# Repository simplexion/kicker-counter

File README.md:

# Kicker Counter
A simple way to digitize manual kicker counters.

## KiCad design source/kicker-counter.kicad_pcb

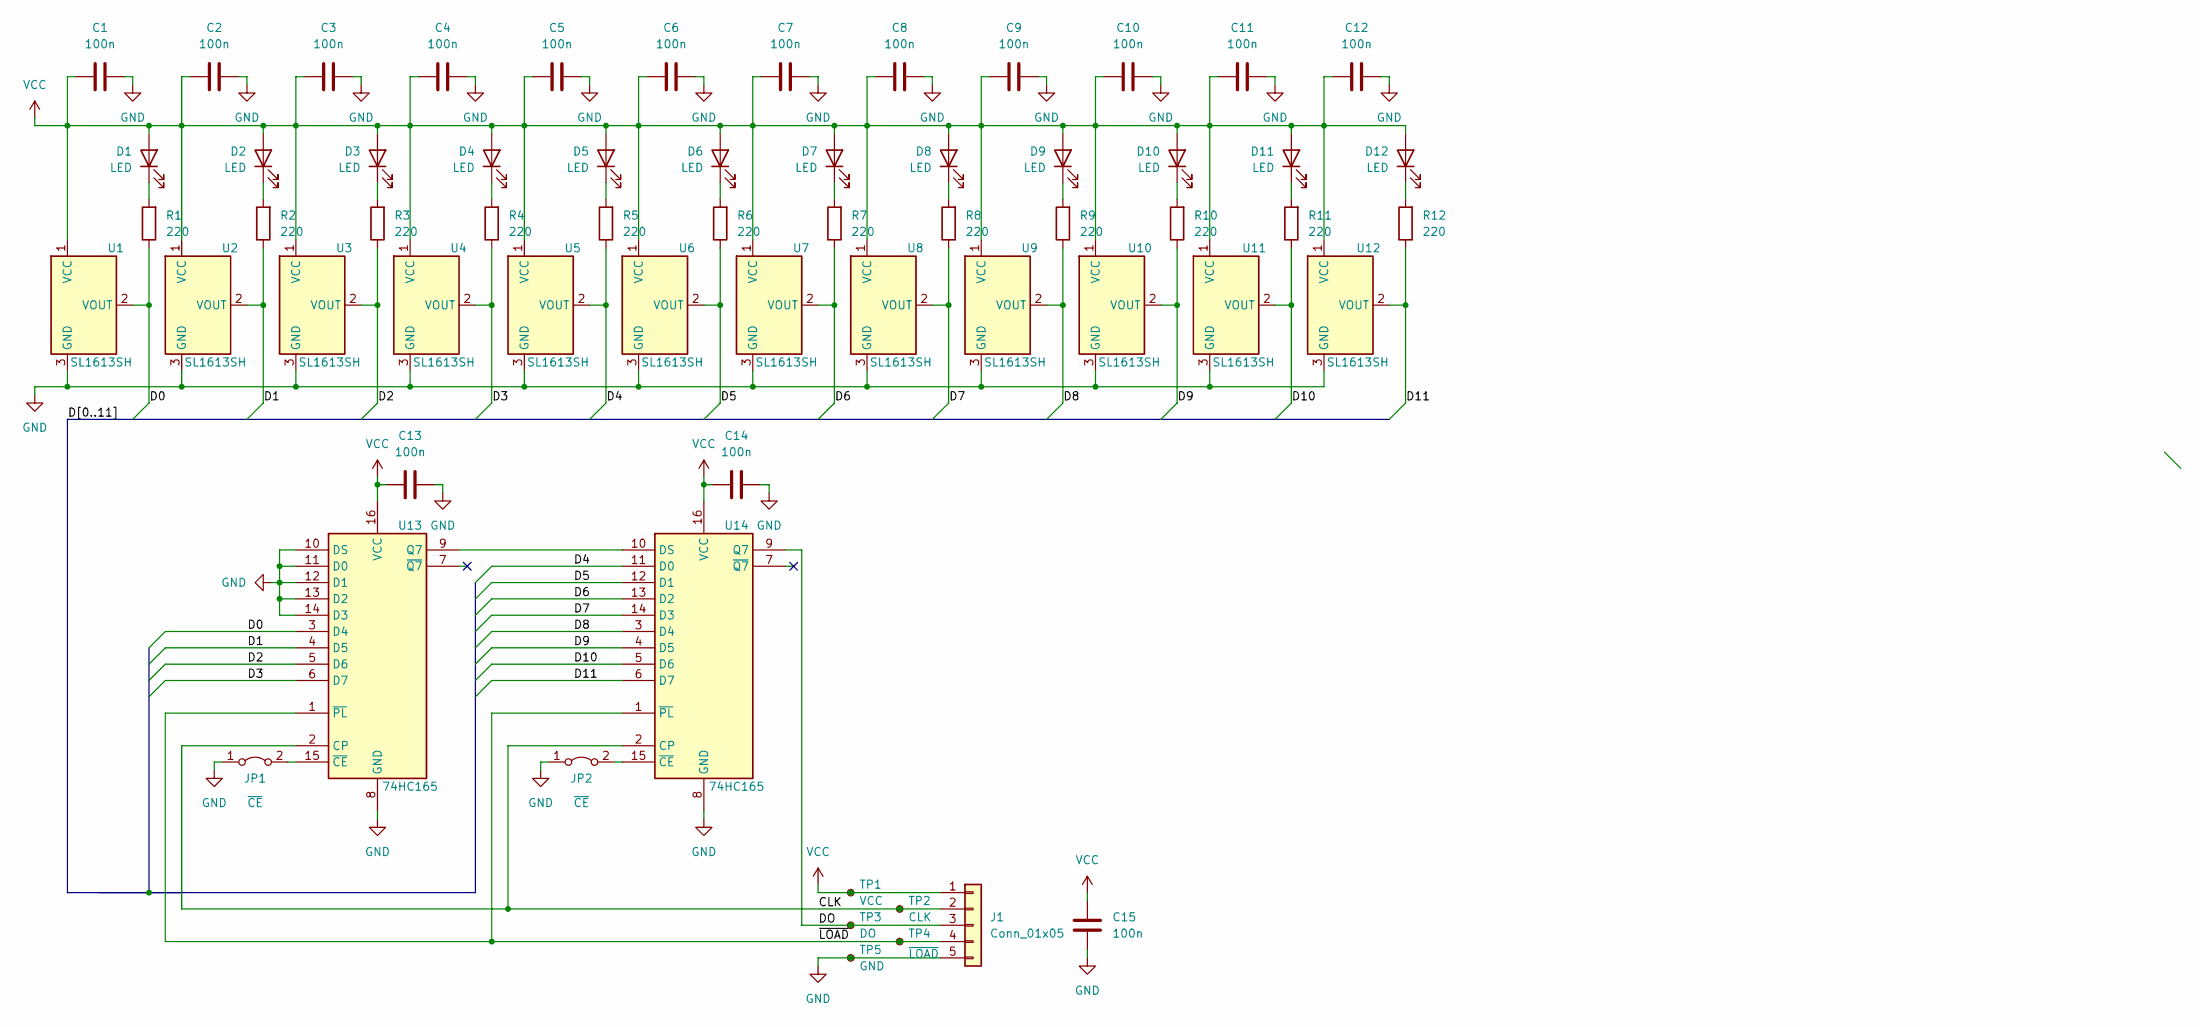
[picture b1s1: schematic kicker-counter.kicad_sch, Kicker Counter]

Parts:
C1, C2, C3, C4, C5, C6, C7, C8, C9, C10, C11, C12, C13, C14, C15: 100n; C_0603_1608Metric; LCSC C42998
D1, D2, D3, D4, D5, D6, D7, D8, D9, D10, D11, D12: LED; LED_0603_1608Metric; LCSC C2290
J1: Conn_01x05
JP1, JP2: ~{CE}; SolderJumper-2_P1.3mm_Bridged_RoundedPad1.0x1.5mm
R1, R2, R3, R4, R5, R6, R7, R8, R9, R10, R11, R12: 220; R_0603_1608Metric; LCSC C114683
TP1: VCC; TestPoint_THTPad_D1.5mm_Drill0.7mm
TP2: CLK; TestPoint_THTPad_D1.5mm_Drill0.7mm
TP3: DO; TestPoint_THTPad_D1.5mm_Drill0.7mm
TP4: ~{LOAD}; TestPoint_THTPad_D1.5mm_Drill0.7mm
TP5: GND; TestPoint_THTPad_D1.5mm_Drill0.7mm
U1, U2, U3, U4, U5, U6, U7, U8, U9, U10, U11, U12: SL1613SH; SOT-23; LCSC C498207
U13, U14: 74HC165; TSSOP-16_4.4x5mm_P0.65mm; LCSC C80696

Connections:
/CLK: J1.2, TP2.1, U13.2 (CP), U14.2 (CP)
/D0: R1.1, U1.2 (VOUT), U13.3 (D4)
/D1: R2.1, U2.2 (VOUT), U13.4 (D5)
/D2: R3.1, U3.2 (VOUT), U13.5 (D6)
/D3: R4.1, U4.2 (VOUT), U13.6 (D7)
/D4: R5.1, U5.2 (VOUT), U14.11 (D0)
/D5: R6.1, U6.2 (VOUT), U14.12 (D1)
/D6: R7.1, U7.2 (VOUT), U14.13 (D2)
/D7: R8.1, U8.2 (VOUT), U14.14 (D3)
/D8: R9.1, U9.2 (VOUT), U14.3 (D4)
/D9: R10.1, U10.2 (VOUT), U14.4 (D5)
/D10: R11.1, U11.2 (VOUT), U14.5 (D6)
/D11: R12.1, U12.2 (VOUT), U14.6 (D7)
/DO: J1.3, TP3.1, U14.9 (Q7)
/~LOAD: J1.4, TP4.1, U13.1 (~PL), U14.1 (~PL)
GND: C1.1, C2.1, C3.1, C4.1, C5.1, C6.1, C7.1, C8.1, C9.1, C10.1, C11.1, C12.1, C13.2, C14.2, C15.1, J1.5, JP1.1 (A), JP2.1 (A), TP5.1, U1.3 (GND), U2.3 (GND), U3.3 (GND), U4.3 (GND), U5.3 (GND), U6.3 (GND), U7.3 (GND), U8.3 (GND), U9.3 (GND), U10.3 (GND), U11.3 (GND), U12.3 (GND), U13.8 (GND), U13.10 (DS), U13.11 (D0), U13.12 (D1), U13.13 (D2), U13.14 (D3), U14.8 (GND)
unnamed: D1.1 (K), R1.2
unnamed: D2.1 (K), R2.2
unnamed: D3.1 (K), R3.2
unnamed: D4.1 (K), R4.2
unnamed: D5.1 (K), R5.2
unnamed: D6.1 (K), R6.2
unnamed: D7.1 (K), R7.2
unnamed: D8.1 (K), R8.2
unnamed: D9.1 (K), R9.2
unnamed: D10.1 (K), R10.2
unnamed: D11.1 (K), R11.2
unnamed: D12.1 (K), R12.2
unnamed: JP1.2 (B), U13.15 (~CE)
unnamed: JP2.2 (B), U14.15 (~CE)
unnamed: U13.9 (Q7), U14.10 (DS)
VCC: C1.2, C2.2, C3.2, C4.2, C5.2, C6.2, C7.2, C8.2, C9.2, C10.2, C11.2, C12.2, C13.1, C14.1, C15.2, D1.2 (A), D2.2 (A), D3.2 (A), D4.2 (A), D5.2 (A), D6.2 (A), D7.2 (A), D8.2 (A), D9.2 (A), D10.2 (A), D11.2 (A), D12.2 (A), J1.1, TP1.1, U1.1 (VCC), U2.1 (VCC), U3.1 (VCC), U4.1 (VCC), U5.1 (VCC), U6.1 (VCC), U7.1 (VCC), U8.1 (VCC), U9.1 (VCC), U10.1 (VCC), U11.1 (VCC), U12.1 (VCC), U13.16 (VCC), U14.16 (VCC)

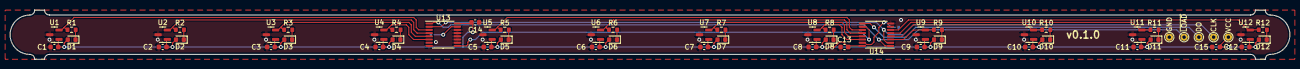
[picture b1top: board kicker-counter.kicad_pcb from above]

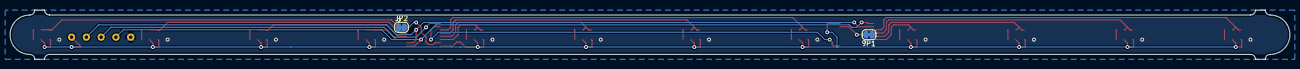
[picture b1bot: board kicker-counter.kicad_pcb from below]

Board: 2 copper layers, 260.0 x 10.0 mm, 60 parts (2 on the bottom side), 32 nets.

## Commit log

2022-05-04 initial design
2022-05-04 edit readme
